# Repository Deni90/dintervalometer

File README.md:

#Dintervalometer

Intervalometer for DSLR cameras based on Atmega328p and PCD8544 LCD display

##Description

Dintervalometer (Deni's intervalometer) is a custom made intervalometer for DSLR cameras. The main purpose is to enable cameras to shoot time lapses and to allow shutter speed longer than the 30s.

##Features

- Intervalometer
- Bulb mode
- Backlight with variable brightness
- Charging via USB

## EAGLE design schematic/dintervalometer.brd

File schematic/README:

Schematic and PCB are created with Cadsoft EAGLE

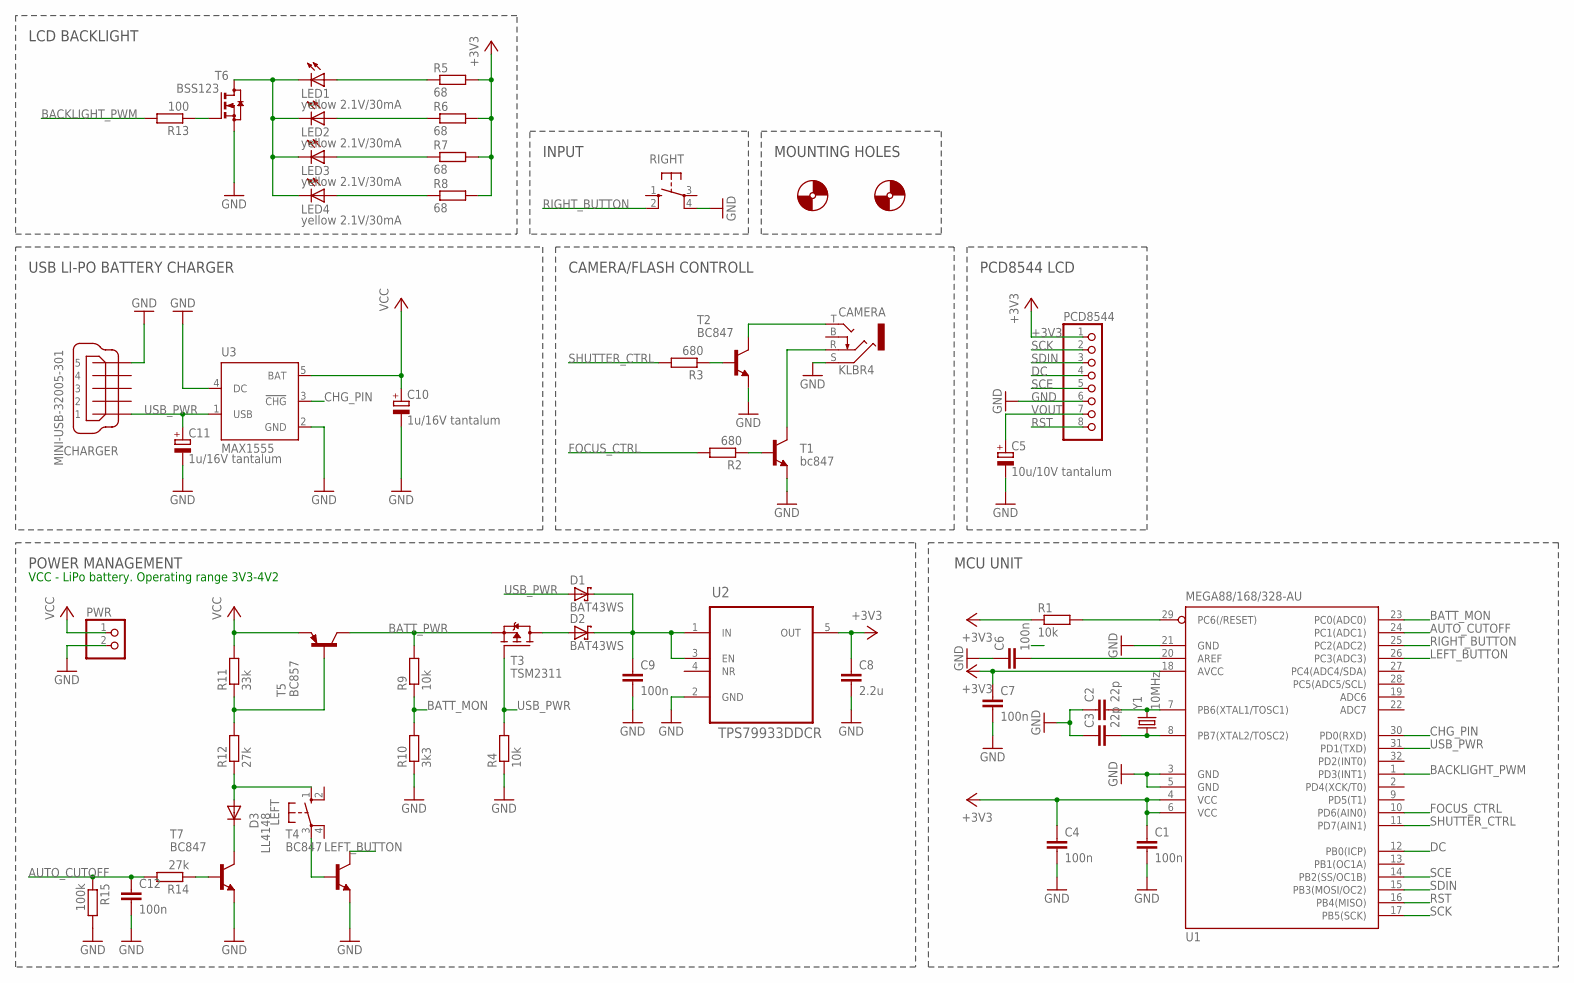
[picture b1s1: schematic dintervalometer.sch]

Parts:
C1, C4, C6, C7, C9, C12: 100n; C0805
C2, C3: 22p; C0805
C5: 10u/10V tantalum; SMC_A
C8: 2.2u; C0805
C10, C11: 1u/16V tantalum; SMC_A
CAMERA: KLBR4
CHARGER: MINI-USB-32005-301; 32005-301
D1, D2: BAT43WS; SOD323_ST
D3: LL4148; SOD80C
LED1, LED2, LED3, LED4: yellow 2.1V/30mA; CHIP-LED0805
LEFT: 10-XX; B3F-10XX
PCD8544: PINHD-1X8; 1X08
PWR: PINHD-1X2/90; 1X02/90
R1, R4, R9: 10k; M0805
R2, R3: 680; M0805
R5, R6, R7, R8: 68; M0805
R10: 3k3; M0805
R11: 33k; M0805
R12, R14: 27k; M0805
R13: 100; M0805
R15: 100k; M0805
RIGHT: 10-XX; B3F-10XX; MPN B3F-1000
T1: bc847; SOT23-BEC
T2: BC847; SOT23-BEC
T3: TSM2311; SOT23
T4, T7: BC847; SOT23
T5: BC857; SOT23-BEC
T6: BSS123; SOT23
U1: MEGA88/168/328-AU; TQFP32-08
U2: TPS79933DDCR; SOT95P290X145-5N
U3: MAX1555; SOT23-5L
X1, X3: 2.8MM_HOLE
Y1: 10MHz; 5X3.2MM

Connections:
+3V3: C1.1, C4.1, C7.1, C8.1, PCD8544.1, R1.1, R5.2, R6.2, R7.2, R8.2, U1.4 (VCC), U1.6 (VCC), U1.18 (AVCC), U2.5 (OUT)
AUTO_CUTOFF: C12.1, R14.2, R15.1, U1.24 (PC1(ADC1))
BACKLIGHT_PWM: R13.2, U1.1 (PD3(INT1))
BATT_MON: R9.1, R10.2, U1.23 (PC0(ADC0))
BATT_PWR: R9.2, T3.2 (S), T5.C
CHG_PIN: U1.30 (PD0(RXD)), U3.3 (!CHG)
DC: PCD8544.4, U1.12 (PB0(ICP))
FOCUS_CTRL: R2.2, U1.10 (PD6(AIN0))
GND: C1.2, C2.1, C3.1, C4.2, C5.-, C6.1, C7.2, C8.2, C9.2, C10.-, C11.-, C12.2, CAMERA.S, CHARGER.5, PCD8544.6, PWR.2, R4.1, R10.1, R15.2, RIGHT.4 (P1), T1.E, T2.E, T4.2 (E), T6.2 (S), T7.2 (E), U1.3 (GND), U1.5 (GND), U1.21 (GND), U2.2 (GND), U3.2 (GND), U3.4 (DC)
LEFT_BUTTON: T4.3 (C), U1.26 (PC3(ADC3))
unnamed: R1.2, U1.29 (PC6(/RESET))
unnamed: C2.2, U1.7 (PB6(XTAL1/TOSC1)), Y1.3 (2)
unnamed: C3.2, U1.8 (PB7(XTAL2/TOSC2)), Y1.1
unnamed: R3.1, T2.B
unnamed: R11.1, R12.2, T5.B
unnamed: C6.2, U1.20 (AREF)
unnamed: LED1.A, R5.1
unnamed: D3.A, LEFT.1 (S), R12.1
unnamed: D3.C, T7.3 (C)
unnamed: D2.A, T3.3 (D)
unnamed: LEFT.3, T4.1 (B)
unnamed: LED1.C, LED2.C, LED3.C, LED4.C, T6.3 (D)
unnamed: R2.1, T1.B
unnamed: R13.1, T6.1 (G)
unnamed: LED2.A, R6.1
unnamed: LED3.A, R7.1
unnamed: LED4.A, R8.1
unnamed: CAMERA.T, T2.C
unnamed: CAMERA.R, T1.C
unnamed: R14.1, T7.1 (B)
unnamed: C9.1, D1.C, D2.C, U2.1 (IN), U2.3 (EN)
RIGHT_BUTTON: RIGHT.2 (S1), U1.25 (PC2(ADC2))
RST: PCD8544.8, U1.16 (PB4(MISO))
SCE: PCD8544.5, U1.14 (PB2(SS/OC1B))
SCK: PCD8544.2, U1.17 (PB5(SCK))
SDIN: PCD8544.3, U1.15 (PB3(MOSI/OC2))
SHUTTER_CTRL: R3.2, U1.11 (PD7(AIN1))
USB_PWR: C11.+, CHARGER.1, D1.A, R4.2, T3.1 (G), U1.31 (PD1(TXD)), U3.1 (USB)
VCC: C10.+, PWR.1, R11.2, T5.E, U3.5 (BAT)
VOUT: C5.+, PCD8544.7

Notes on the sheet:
VCC - LiPo battery. Operating range 3V3-4V2
USB LI-PO BATTERY CHARGER
LCD BACKLIGHT
CAMERA/FLASH CONTROLL
PCD8544 LCD
MOUNTING HOLES
POWER MANAGEMENT
MCU UNIT
INPUT

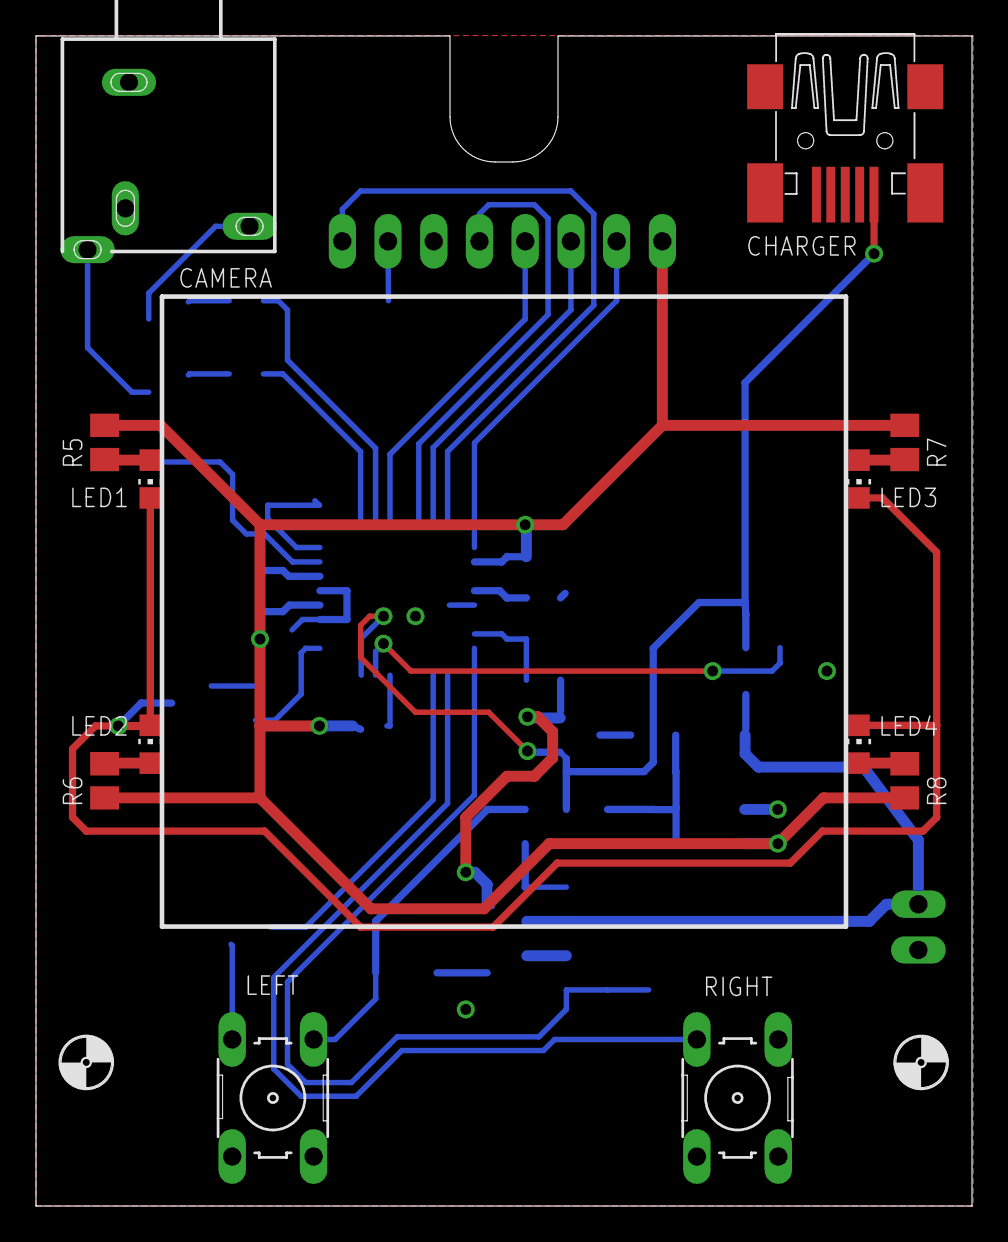
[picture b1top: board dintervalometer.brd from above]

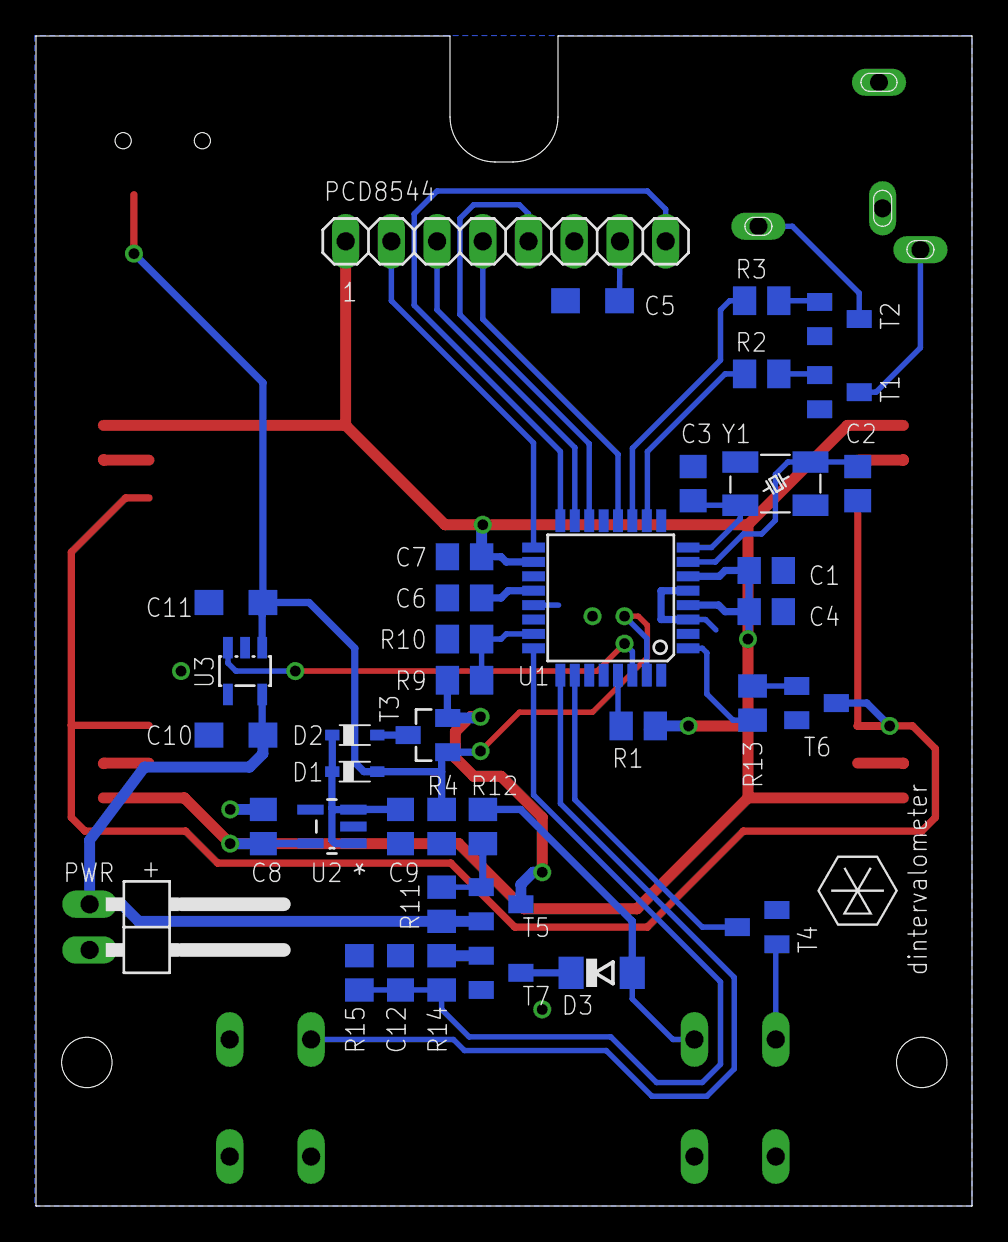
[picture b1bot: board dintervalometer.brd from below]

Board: 2 copper layers, 52.0 x 65.0 mm, 53 parts (39 on the bottom side), 40 nets.

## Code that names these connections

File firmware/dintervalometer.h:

/*
 *  dintervalometer.h
 *
 *  "THE DON'T-CARE LICENCE"
 *  I don't care, do whatever you want with this file.
 *
 *  Author: Daniel Knezevic
 *  E-mail: danielknezevic90<at>gmail.com
 */

#ifndef DINTERVALOMETER_H_
#define DINTERVALOMETER_H_

#define TRUE                    1
#define FALSE                   0

#define ONE_SECOND              1000    // milliseconds

#define BUTTON_HOLD_INTERVAL    1000    // miliseconds to pronounce button as held rather than pressed
#define UNLOCK_INTERVAL         2000    // milliseconds
#define TIMEOUT_INTERVAL        2000    // milliseconds
#define DEBOUNCE_INTERVAL       50      // milliseconds

#define LEFT_BUTTON_DDR         DDRC
#define LEFT_BUTTON_PIN         PINC
#define LEFT_BUTTON_PORT        PORTC
#define LEFT_BUTTON_IO          PC3

#define RIGHT_BUTTON_DDR        DDRC
#define RIGHT_BUTTON_PIN        PINC
#define RIGHT_BUTTON_PORT       PORTC
#define RIGHT_BUTTON_IO         PC2

#define AUTO_CUTOFF_DDR         DDRC
#define AUTO_CUTOFF_PIN         PINC
#define AUTO_CUTOFF_PORT        PORTC
#define AUTO_CUTOFF_IO          PC1

#define SHUTTER_DDR             DDRD
#define SHUTTER_PIN             PIND
#define SHUTTER_PORT            PORTD
#define SHUTTER_IO              PD7

#define FOCUS_DDR               DDRD
#define FOCUS_PIN               PIND
#define FOCUS_PORT              PORTD
#define FOCUS_IO                PD6

#define CHG_DDR                 DDRD
#define CHG_PIN                 PIND
#define CHG_PORT                PORTD
#define CHG_IO                  PD0

#define USB_PWR_DDR             DDRD
#define USB_PWR_PIN             PIND
#define USB_PWR_PORT            PORTD
#define USB_PWR_IO              PD1

#define BACKLIGHT_DDR           DDRD
#define BACKLIGHT_PIN           PIND
#define BACKLIGHT_PORT          PORTD
#define BACKLIGHT_IO            PD3
#define BACKLIGHT_DURATION      10000   // millisecond

#define BLINK_PERIOD           1000     // millisecons
#define ICON_WIDTH              8

#define MAX_BATTERY_VOLTAGE     4200    // mV
#define MIN_BATTERY_VOLTAGE     3600    // mV
#define BATTERY_MONITOR_PERIOD  60000   // milliseconds

#define PN_JUNCTION             600     // mV

#define BACKLIGHT_INTENSITY     63

typedef enum state_e {
    MAIN_MENU = 0,
    INTERVALOMETER_MENU,
    BULB_MODE_MENU,
    SETTINGS,
    OFF,
    INTERVALOMETER,
    BULB_MODE,
    INIT,
    NUM_OF_STATES
} state_t;

typedef state_t state_func_t(void);

typedef struct intervalometer_s {
    uint16_t delay;
    uint16_t period;
    uint16_t shots;
    uint8_t prefocus;
} intervalometer_t;

typedef struct bulb_mode_s {
    uint16_t delay;
    uint16_t duration;
} bulb_mode_t;

typedef struct settings_s {
    uint8_t backlight_intensity;
    uint16_t battery_auto_cutoff;   //mV
} settings_t;

#endif /* DINTERVALOMETER_H_ */

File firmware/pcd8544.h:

#ifndef _PCD8544_LCD_H_
#define _PCD8544_LCD_H_

#include <avr/io.h>

#define DC              PB0
#define SCE             PB2
#define RST             PB4
#define SCK             PB5
#define MOSI            PB3

#define SPI_DDR         DDRB
#define SPI_PORT        PORTB

#define SET_DC_PIN      SPI_PORT |= (1 << DC)
#define CLEAR_DC_PIN    SPI_PORT &= ~(1 << DC)
#define SET_SCE_PIN     SPI_PORT |= (1 << SCE)
#define CLEAR_SCE_PIN   SPI_PORT &= ~(1 << SCE)
#define SET_RST_PIN     SPI_PORT |= (1 << RST)
#define CLEAR_RST_PIN   SPI_PORT &= ~(1 << RST)

#define LCD_WIDTH       84  // 84pixels
#define LCD_HEIGHT      6   // 6 cells of 8 pixels -> 6 * 8 = 48

// LCD_putc() "type" parameter options:
#define LCD_TYP_NORM    0b00000000    // normal
#define LCD_TYP_INV     0b10000000    // inverted text (white on black bg)
#define LCD_TYP_NOSPC   0b00000100    // no spacing between characters
#define LCD_TYP_UP1     0b00000001    // moved 1 pixel up
#define LCD_TYP_UP2     0b00000010    // moved 2 pixels up
#define LCD_TYP_ULI     0b00001000    // underlined with black pixel
#define LCD_TYP_ULIW    0b00010000    // underlined with white pixel
#define LCD_TYP_CKNL    0b00100000    // check for automatic new-line (used in in lcd_puts())

extern void TIMER_delay_ms(uint16_t _mS);

/**
 * Name         :  LCD_init
 * Description  :  Initializes the LCD display.
 * Argument(s)  :  None.
 * Return value :  None.
 */
void LCD_init(void);

/**
 * Name         :  LCD_writeCommand
 * Description  :  Sends command to display controller.
 * Argument(s)  :  command -> command to be sent
 * Return value :  None.
 */
void LCD_writeCommand(char command);

/**
 * Name         :  LCD_writeData
 * Description  :  Sends Data to display controller.
 * Argument(s)  :  Data -> Data to be sent
 * Return value :  None.
 */
void LCD_writeData(char data);

/**
 * Name         :  LCD_goto
 * Description  :  Sets cursor location to xy location corresponding to basic font size.
 * Argument(s)  :  x -> range: 0 to 83
 *                 y -> range: 0 to 5
 * Return value :  None.
 */
void LCD_goto(uint8_t x, uint8_t y);

/**
 * Name         :  LCD_clear
 * Description  :  Clears the display
 * Argument(s)  :  None.
 * Return value :  None.
 */
void LCD_clear(void);

/**
 * Name         :  LCD_clearLine
 * Description  :  Clears one line on LCD
 * Argument(s)  :  line -> line to be cleared
 * Return value :  None.
 */
void LCD_clearLine(uint8_t line);

/**
 * Name         :  LCD_putc
 * Description  :  Puts a character on lcd using font defined in .h file. Code borrowed from:
 *                 http://www.elektronika.ba/789/reverse-geocaching-geogame-v1/
 * Argument(s)  :  character -> character to be shown on lcd
 *                 type -> [0]0000000 = 0=normal text,1=inverted text
 *                          000000[00] = 00=no vertical movement, 01=moved 1 pixes up, 10=moved 2 pixels up
 *                          00000[0]00 = 0=with spacing, 1=without character spacing
 *                          000[0]0000 = 0=normal, 1=underlined(bottom pixel set)
 *                          and many more: see .h file for other LCD_TYP... constants
 * Return value :  None.
 */
void LCD_putc(char character , uint8_t type);

/**
 * Name         :  LCD_puts
 * Description  :  Put a null-terminated string on lcd. Code borrowed from:
 *                 http://www.elektronika.ba/789/reverse-geocaching-geogame-v1/
 * Argument(s)  :  s -> string
 *                 type -> [0]0000000 = 0=normal text,1=inverted text
 *                          000000[00] = 00=no vertical movement, 01=moved 1 pixes up, 10=moved 2 pixels up
 *                          00000[0]00 = 0=with spacing, 1=without character spacing
 *                          000[0]0000 = 0=normal, 1=underlined(bottom pixel set)
 *                          and many more: see .h file for other LCD_TYP... constants
 * Return value :  None.
 */
void LCD_puts(const __flash char *s, uint8_t type);

/**
 * Name         :  LCD_putcBig
 * Description  :  Puts a character on lcd using font defined in .h file, but the
 *                 size of the font is doubled.
 * Argument(s)  :  character -> character to be shown on lcd
 *                 type -> [0]0000000 = 0=normal text,1=inverted text
 *                          000000[00] = 00=no vertical movement, 01=moved 1 pixes up, 10=moved 2 pixels up
 *                          00000[0]00 = 0=with spacing, 1=without character spacing
 *                          000[0]0000 = 0=normal, 1=underlined(bottom pixel set)
 *                          and many more: see .h file for other LCD_TYP... constants
 * Return value :  None.
 */
void LCD_putcBig(char character, uint8_t type);

/**
 * Name         :  LCD_putCustomChar
 * Description  :  Puts a custom haracter on the lcd.
 * Argument(s)  :  ch -> character to be shown on lcd
 *                 type -> [0]0000000 = 0=normal text,1=inverted text
 *                          000000[00] = 00=no vertical movement, 01=moved 1 pixes up, 10=moved 2 pixels up
 *                 width -> width of the custom character
 * Return value :  None.
 */
void LCD_putCustomChar(const __flash char *ch, uint8_t width, uint8_t type);

/**
 * Name         :  LCD_writeUnsignedValue
 * Description  :  Puts unsigned value on lcd. Code borrowed from:
 *                 http://www.elektronika.ba/789/reverse-geocaching-geogame-v1/
 * Argument(s)  :  value -> unsigned value to be shown on lcd
 *                 type -> [0]0000000 = 0=normal text,1=inverted text
 *                          000000[00] = 00=no vertical movement, 01=moved 1 pixes up, 10=moved 2 pixels up
 *                          00000[0]00 = 0=with spacing, 1=without character spacing
 *                          000[0]0000 = 0=normal, 1=underlined(bottom pixel set)
 *                          and many more: see .h file for other LCD_TYP... constants
 * Return value :  None.
 */
void LCD_writeUnsignedValue(uint32_t value, uint8_t type);

#endif  // _PCD8544_LCD_H_

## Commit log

2016-03-31 Code cleanup
    Bugfix, removed unused enum "SENSOR" from states
2016-04-07 Simplified backlight and changed battery monitor
2016-05-17 Fixed reading battery voltage
